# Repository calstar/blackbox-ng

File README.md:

View this project on [CADLAB.io](https://cadlab.io/project/2320). 

# blackbox-ng
This is the third major revision of STAR's black box project. Previous versions may be found on this git, and even older versions may be found on grabcad.

The major changes in this revision are the switch to kicad, the adjustment of the mounting holes pattern, and the switch to a more reliable linear regulator.

The project is seperated into a main logging board, and several spi daughter boards which can be chained together on an ffc cable and mounted about the vehicle.

## Daughter Boards

At present all daughter boards use jumpers to select the appropriate chipselect lines, but pin mappings are designed to allow us to chain an arbitrary number of devices on a single chain using 74 series shift registers. They also all share a common hole pattern and form factor.

### adxl372

This daughter board has a footprint for the adxl372, as well as a footprint for it's breakout board. The adxl372 is a relatively high bandwidth mems accelerometer that we plan on using to derive vibration data from.

### Debug Board (aka vronsky-daughter)

This board has a .1" header so that it can be used to access the signals of all the pins on its connector. It also has a footprint for a high speed barometric pressure sensor, in order to serve as a backup logging system for the pitot tube project.

### BMP388

This board is currently under development by Zitao and an attachment for STAR's next standard barometric pressure sensor. It is not yet production ready, but will likely be going out in the next board run.

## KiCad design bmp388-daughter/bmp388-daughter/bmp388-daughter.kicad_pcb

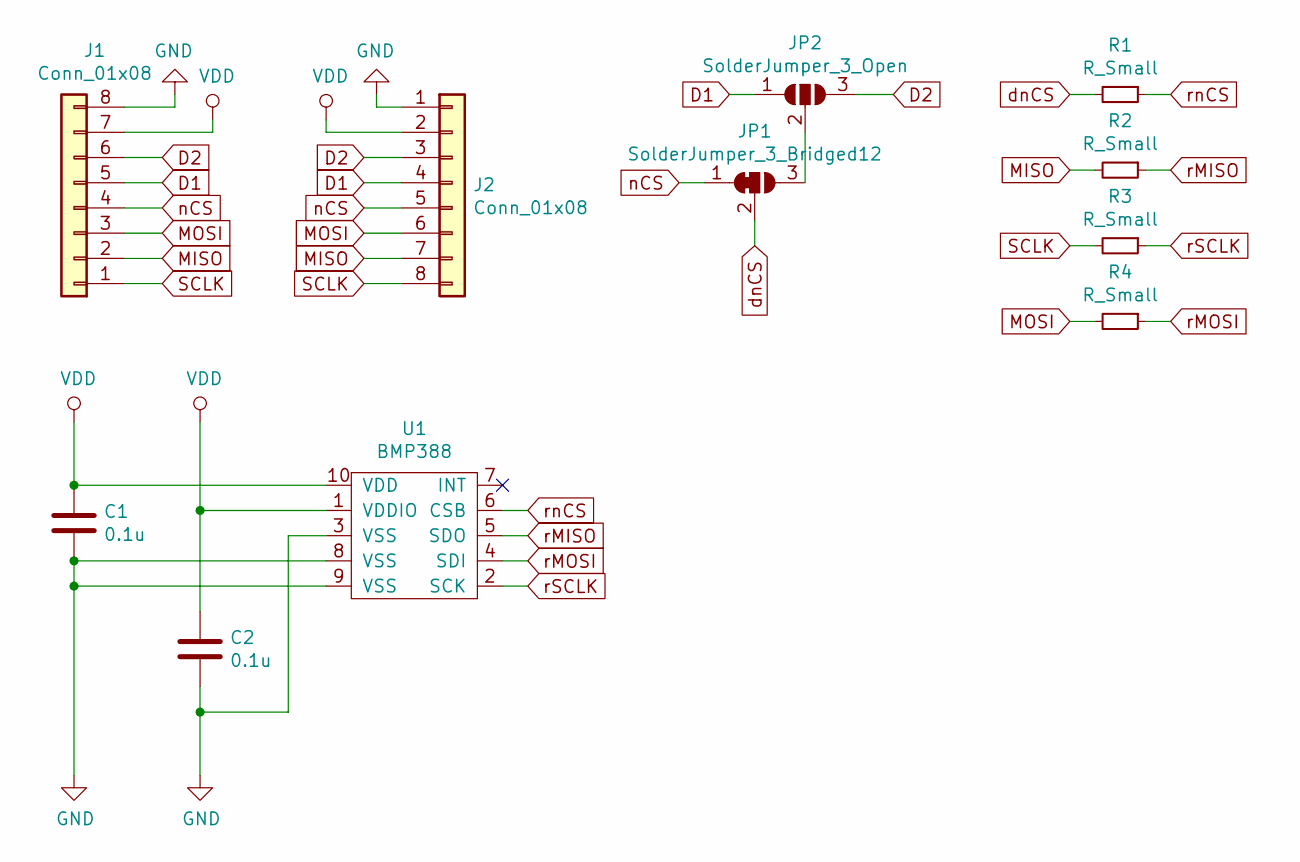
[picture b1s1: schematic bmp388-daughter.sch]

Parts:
C1, C2: 0.1u; C_0603_1608Metric_Pad1.05x0.95mm_HandSolder
J1, J2: Conn_01x08; 505110-0892
JP1: SolderJumper_3_Bridged12; SolderJumper-3_P1.3mm_Bridged2Bar12_Pad1.0x1.5mm
JP2: SolderJumper_3_Open; SolderJumper-3_P1.3mm_Open_Pad1.0x1.5mm
R1, R2, R3, R4: R_Small; R_0603_1608Metric_Pad1.05x0.95mm_HandSolder
U1: BMP388

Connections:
D1: J1.5, J2.4, JP2.1 (A)
D2: J1.6, J2.3, JP2.3 (B)
GND: C1.2, C2.2, J1.8, J2.1, U1.3 (VSS), U1.8 (VSS), U1.9 (VSS)
MISO: J1.2, J2.7, R2.2
MOSI: J1.3, J2.6, R4.2
unnamed: JP1.3 (B), JP2.2 (C)
SCLK: J1.1, J2.8, R3.2
VDD: C1.1, C2.1, J1.7, J2.2, U1.1 (VDDIO), U1.10 (VDD)
dnCS: JP1.2 (C), R1.2
nCS: J1.4, J2.5, JP1.1 (A)
rMISO: R2.1, U1.5 (SDO)
rMOSI: R4.1, U1.4 (SDI)
rSCLK: R3.1, U1.2 (SCK)
rnCS: R1.1, U1.6 (CSB)

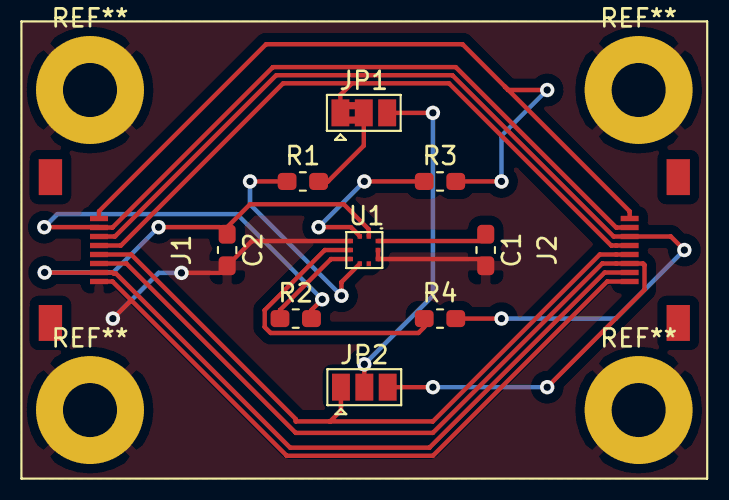
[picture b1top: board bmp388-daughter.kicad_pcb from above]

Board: 2 copper layers, 11 parts (0 on the bottom side), 14 nets.

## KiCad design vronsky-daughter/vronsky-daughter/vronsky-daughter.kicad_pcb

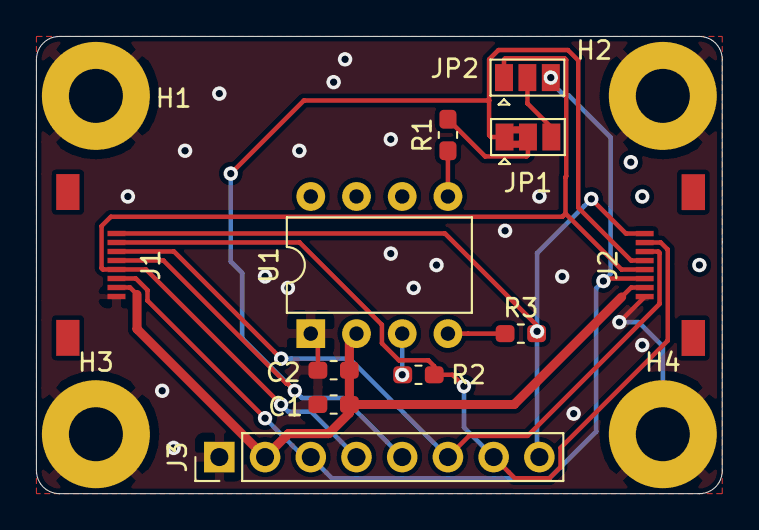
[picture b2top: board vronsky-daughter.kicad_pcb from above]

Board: 2 copper layers, 38.1 x 25.4 mm, 15 parts (0 on the bottom side), 13 nets.

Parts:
C1: 1u; C_0603_1608Metric_Pad1.05x0.95mm_HandSolder
C2: 0.1u; C_0603_1608Metric_Pad1.05x0.95mm_HandSolder
H1, H2, H3, H4: MountingHole_3mm_Pad
J1, J2: Conn_01x08; 505110-0892
J3: Conn_01x08_Male; PinHeader_1x08_P2.54mm_Vertical
JP1: SolderJumper_3_Bridged12; SolderJumper-3_P1.3mm_Bridged2Bar12_Pad1.0x1.5mm
JP2: SolderJumper_3_Open; SolderJumper-3_P1.3mm_Open_Pad1.0x1.5mm
R1, R2, R3: R_Small; R_0603_1608Metric_Pad1.05x0.95mm_HandSolder
U1: HSCSPI; DIP-8_W7.62mm

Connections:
D1: J1.5, J2.4, J3.4, JP2.1
D2: J1.6, J2.3, J3.3, JP2.3
GND: C1.1, C2.1, H1.1, H2.1, H3.1, H4.1, J1.8, J2.1, J3.1, U1.1
MISO: J1.2, J2.7, J3.7, R2.2
MOSI: J1.3, J2.6, J3.6
unnamed: JP1.3, JP2.2
SCLK: J1.1, J2.8, J3.8, R3.2
VDD: C1.2, C2.2, J1.7, J2.2, J3.2, U1.2
dnCS: JP1.2, R1.2
nCS: J1.4, J2.5, J3.5, JP1.1
rMISO: R2.1, U1.3
rSCLK: R3.1, U1.4
rnCS: R1.1, U1.5

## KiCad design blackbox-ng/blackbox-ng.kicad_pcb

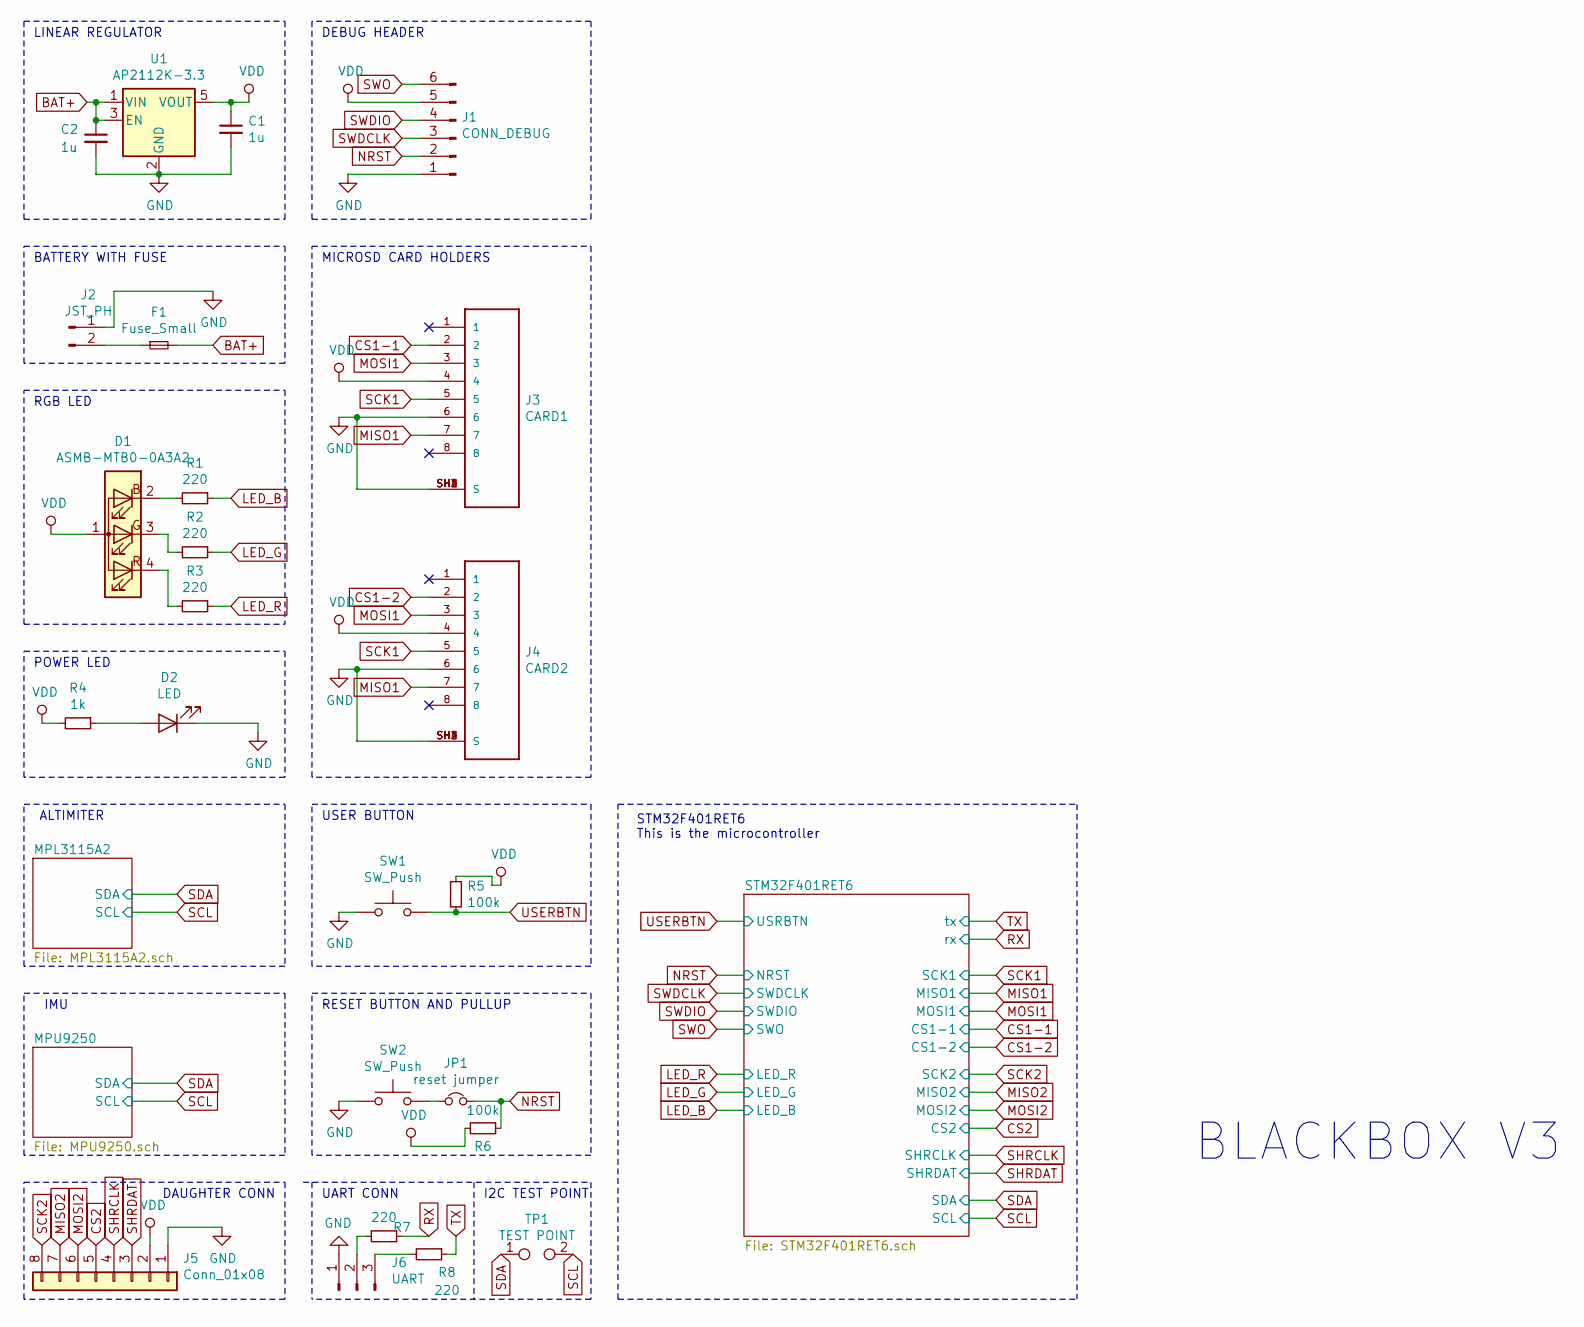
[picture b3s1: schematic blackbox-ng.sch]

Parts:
C1, C2: 1u; C_0603_1608Metric_Pad1.05x0.95mm_HandSolder
D1: ASMB-MTB0-0A3A2; LED_Avago_PLCC4_3.2x2.8mm_CW
D2: LED; LED_0603_1608Metric_Castellated
F1: Fuse_Small; Fuse_0603_1608Metric_Pad1.05x0.95mm_HandSolder
J1: CONN_DEBUG; PinHeader_1x06_P2.54mm_Vertical
J2: JST_PH; JST_PH_B2B-PH-K_1x02_P2.00mm_Vertical
J3: CARD1; MOLEX_500901-0801
J4: CARD2; MOLEX_500901-0801
J5: Conn_01x08; 505110-0892
J6: UART; PinHeader_1x03_P2.54mm_Vertical
JP1: reset jumper; SolderJumper-2_P1.3mm_Bridged2Bar_Pad1.0x1.5mm
R1, R2, R3, R7, R8: 220; R_0603_1608Metric_Pad1.05x0.95mm_HandSolder
R4: 1k; R_0603_1608Metric_Pad1.05x0.95mm_HandSolder
R5, R6: 100k; R_0603_1608Metric_Pad1.05x0.95mm_HandSolder
SW1, SW2: SW_Push; SW_SPST_B3S-1000
TP1: TEST POINT; TestPoint_2Pads_Pitch2.54mm_Drill0.8mm
U1: AP2112K-3.3; SOT-23-5

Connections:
BAT+: C2.1, F1.2, U1.1 (VIN), U1.3 (EN)
CS1-1: J3.2; also elsewhere on the board
CS1-2: J4.2; also elsewhere on the board
CS2: J5.5; also elsewhere on the board
GND: C1.2, C2.2, D2.1 (K), J1.1, J2.1, J3.6, J3.SH1 (S), J3.SH2 (S), J3.SH3 (S), J3.SH4 (S), J4.6, J4.SH1 (S), J4.SH2 (S), J4.SH3 (S), J4.SH4 (S), J5.1, J6.1, SW1.1, SW2.1, U1.2 (GND); also elsewhere on the board
LED_B: R1.1; also elsewhere on the board
LED_G: R2.1; also elsewhere on the board
LED_R: R3.1; also elsewhere on the board
MISO1: J3.7, J4.7; also elsewhere on the board
MISO2: J5.7; also elsewhere on the board
MOSI1: J3.3, J4.3; also elsewhere on the board
MOSI2: J5.6; also elsewhere on the board
NRST: J1.2, JP1.2, R6.1; also elsewhere on the board
unnamed: D1.2 (BK), R1.2
unnamed: D1.3 (GK), R2.2
unnamed: D1.4 (RK), R3.2
unnamed: D2.2 (A), R4.1
unnamed: F1.1, J2.2
unnamed: J6.2, R7.2
unnamed: J6.3, R8.2
unnamed: JP1.1, SW2.2
RX: R7.1; also elsewhere on the board
SCK1: J3.5, J4.5; also elsewhere on the board
SCK2: J5.8; also elsewhere on the board
SCL: TP1.2; also elsewhere on the board
SDA: TP1.1; also elsewhere on the board
SHRCLK: J5.4; also elsewhere on the board
SHRDAT: J5.3; also elsewhere on the board
SWDCLK: J1.3; also elsewhere on the board
SWDIO: J1.4; also elsewhere on the board
SWO: J1.6; also elsewhere on the board
TX: R8.1; also elsewhere on the board
USERBTN: R5.2, SW1.2; also elsewhere on the board
VDD: C1.1, D1.1 (A), J1.5, J3.4, J4.4, J5.2, R4.2, R5.1, R6.2, U1.5 (VOUT); also elsewhere on the board

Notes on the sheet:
LINEAR REGULATOR
BATTERY WITH FUSE
RGB LED
POWER LED
ALTIMITER
IMU
DEBUG HEADER
MICROSD CARD HOLDERS
USER BUTTON
RESET BUTTON AND PULLUP
DAUGHTER CONN
UART CONN
I2C TEST POINT
STM32F401RET6 This is the microcontroller
BLACKBOX V3

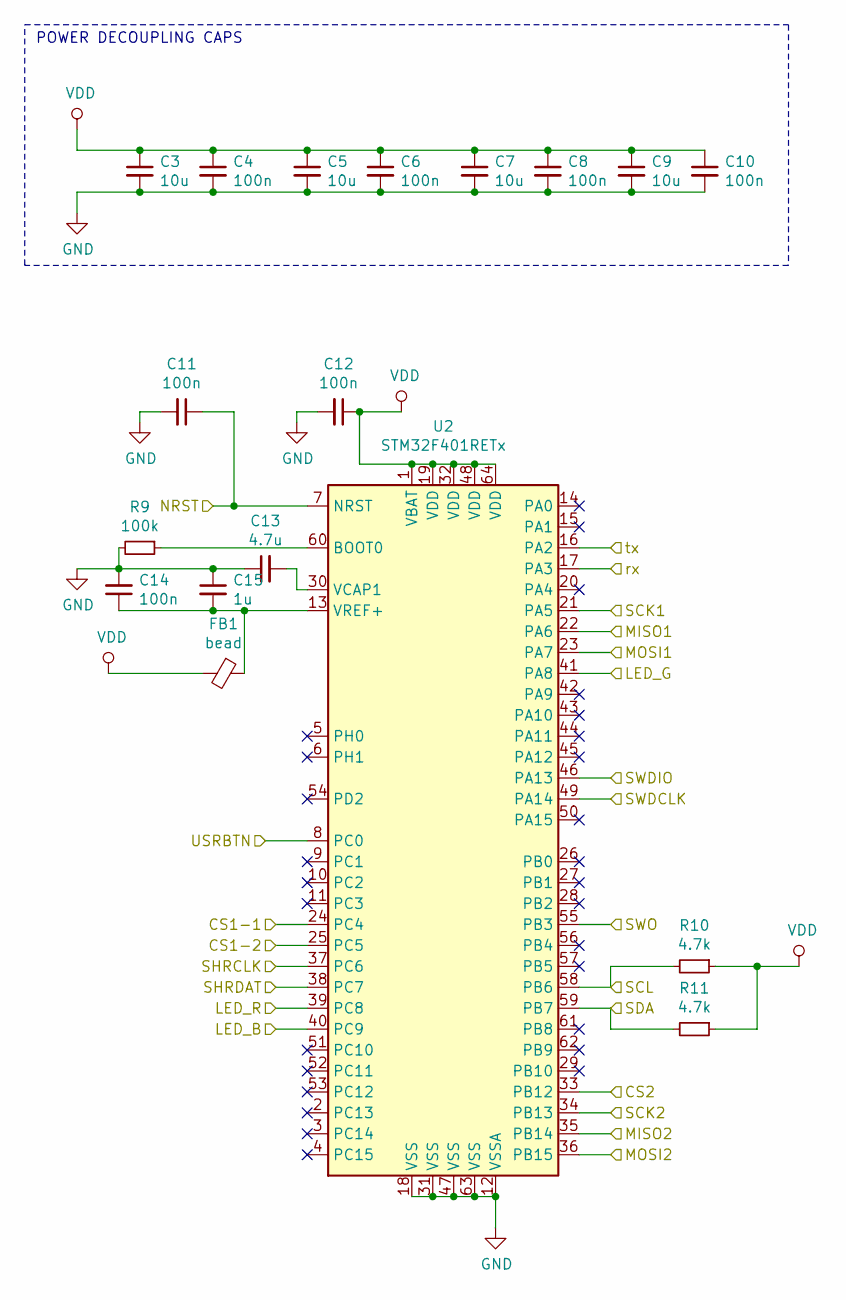
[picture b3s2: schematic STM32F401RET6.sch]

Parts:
C3, C5, C7, C9: 10u; C_0603_1608Metric_Pad1.05x0.95mm_HandSolder
C4, C6, C8, C10, C11, C12, C14: 100n; C_0603_1608Metric_Pad1.05x0.95mm_HandSolder
C13: 4.7u; C_0603_1608Metric_Pad1.05x0.95mm_HandSolder
C15: 1u; C_0603_1608Metric_Pad1.05x0.95mm_HandSolder
FB1: bead; L_0603_1608Metric_Pad1.05x0.95mm_HandSolder
R9: 100k; R_0603_1608Metric_Pad1.05x0.95mm_HandSolder
R10, R11: 4.7k; R_0603_1608Metric_Pad1.05x0.95mm_HandSolder
U2: STM32F401RETx; LQFP-64_10x10mm_P0.5mm

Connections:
CS1-1: U2.24 (PC4); also elsewhere on the board
CS1-2: U2.25 (PC5); also elsewhere on the board
CS2: U2.33 (PB12); also elsewhere on the board
GND: C3.2, C4.2, C5.2, C6.2, C7.2, C8.2, C9.2, C10.2, C11.2, C12.2, C13.1, C14.2, C15.1, R9.2, U2.12 (VSSA), U2.18 (VSS), U2.31 (VSS), U2.47 (VSS), U2.63 (VSS); also elsewhere on the board
LED_B: U2.40 (PC9); also elsewhere on the board
LED_G: U2.41 (PA8); also elsewhere on the board
LED_R: U2.39 (PC8); also elsewhere on the board
MISO1: U2.22 (PA6); also elsewhere on the board
MISO2: U2.35 (PB14); also elsewhere on the board
MOSI1: U2.23 (PA7); also elsewhere on the board
MOSI2: U2.36 (PB15); also elsewhere on the board
NRST: C11.1, U2.7 (NRST); also elsewhere on the board
unnamed: C13.2, U2.30 (VCAP1)
unnamed: C14.1, C15.2, FB1.1, U2.13 (VREF+)
unnamed: R9.1, U2.60 (BOOT0)
RX: U2.17 (PA3); also elsewhere on the board
SCK1: U2.21 (PA5); also elsewhere on the board
SCK2: U2.34 (PB13); also elsewhere on the board
SCL: R10.2, U2.58 (PB6); also elsewhere on the board
SDA: R11.2, U2.59 (PB7); also elsewhere on the board
SHRCLK: U2.37 (PC6); also elsewhere on the board
SHRDAT: U2.38 (PC7); also elsewhere on the board
SWDCLK: U2.49 (PA14); also elsewhere on the board
SWDIO: U2.46 (PA13); also elsewhere on the board
SWO: U2.55 (PB3); also elsewhere on the board
TX: U2.16 (PA2); also elsewhere on the board
USERBTN: U2.8 (PC0); also elsewhere on the board
VDD: C3.1, C4.1, C5.1, C6.1, C7.1, C8.1, C9.1, C10.1, C12.1, FB1.2, R10.1, R11.1, U2.1 (VBAT), U2.19 (VDD), U2.32 (VDD), U2.48 (VDD), U2.64 (VDD); also elsewhere on the board

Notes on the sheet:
POWER DECOUPLING CAPS

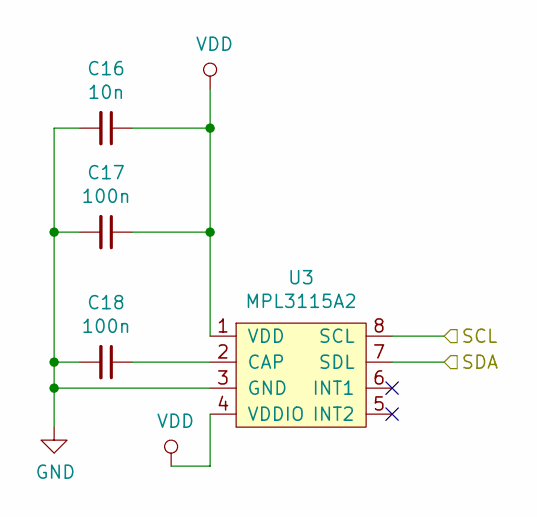
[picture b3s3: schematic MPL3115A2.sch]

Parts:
C16: 10n; C_0603_1608Metric_Pad1.05x0.95mm_HandSolder
C17, C18: 100n; C_0603_1608Metric_Pad1.05x0.95mm_HandSolder
U3: MPL3115A2; NXP_LGA-8_3x5mm_P1.25mm_H1.1mm

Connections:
GND: C16.2, C17.2, C18.2, U3.3 (GND); also elsewhere on the board
unnamed: C18.1, U3.2 (CAP)
SCL: U3.8 (SCL); also elsewhere on the board
SDA: U3.7 (SDL); also elsewhere on the board
VDD: C16.1, C17.1, U3.1 (VDD), U3.4 (VDDIO); also elsewhere on the board

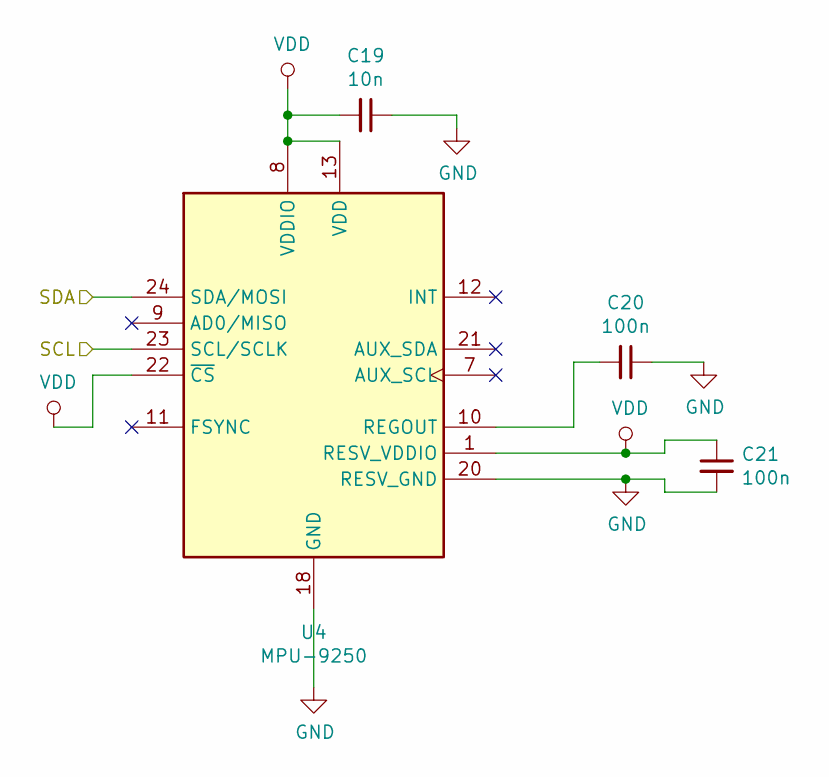
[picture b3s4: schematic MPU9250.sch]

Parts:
C19: 10n; C_0603_1608Metric_Pad1.05x0.95mm_HandSolder
C20, C21: 100n; C_0603_1608Metric_Pad1.05x0.95mm_HandSolder
U4: MPU-9250; InvenSense_QFN-24_3x3mm_P0.4mm

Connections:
GND: C19.1, C20.1, C21.2, U4.18 (GND), U4.20 (RESV_GND); also elsewhere on the board
unnamed: C20.2, U4.10 (REGOUT)
SCL: U4.23 (SCL/SCLK); also elsewhere on the board
SDA: U4.24 (SDA/MOSI); also elsewhere on the board
VDD: C19.2, C21.1, U4.1 (RESV_VDDIO), U4.8 (VDDIO), U4.13 (VDD), U4.22 (~CS); also elsewhere on the board

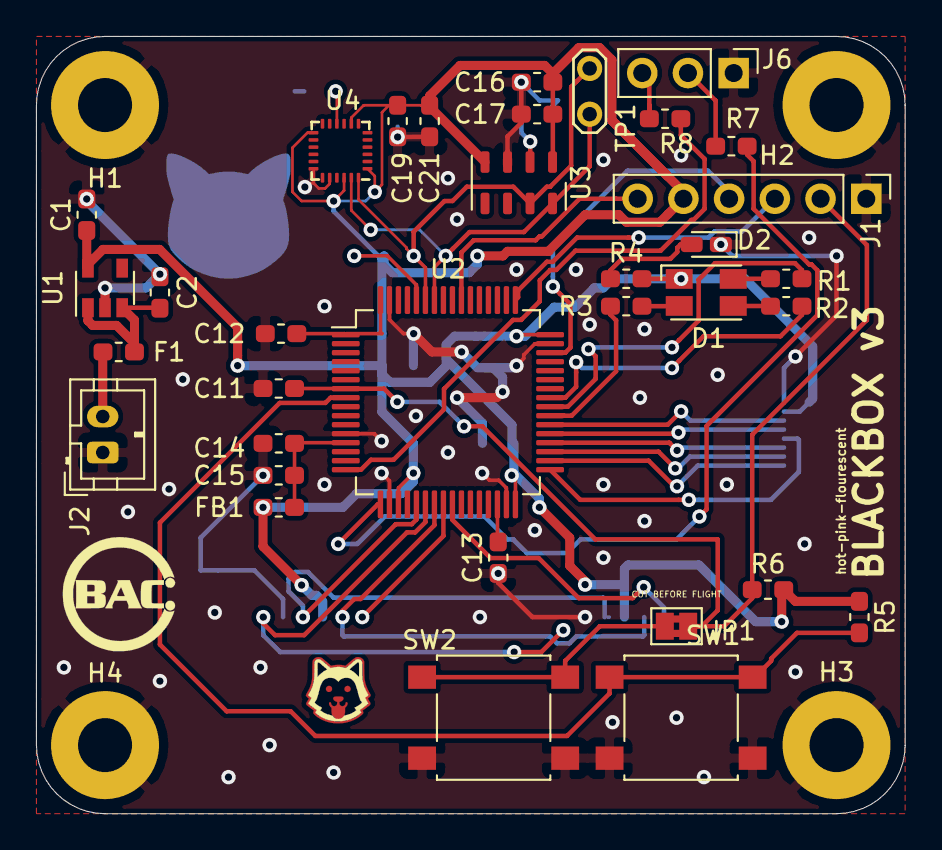
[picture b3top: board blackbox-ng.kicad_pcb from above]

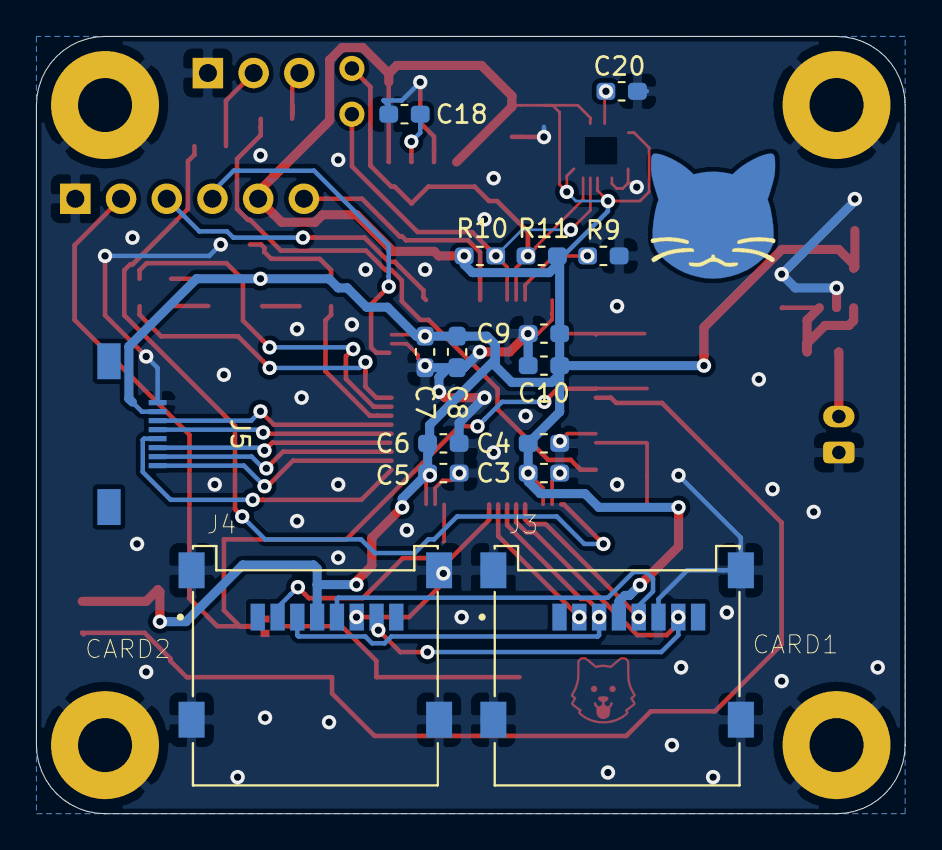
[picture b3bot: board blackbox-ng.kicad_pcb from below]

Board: 2 copper layers, 48.3 x 43.2 mm, 54 parts (16 on the bottom side), 39 nets.

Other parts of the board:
H1, H2, H3, H4: MountingHole_3mm_Pad

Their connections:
GND: H1.1, H2.1, H3.1, H4.1; also elsewhere on the board

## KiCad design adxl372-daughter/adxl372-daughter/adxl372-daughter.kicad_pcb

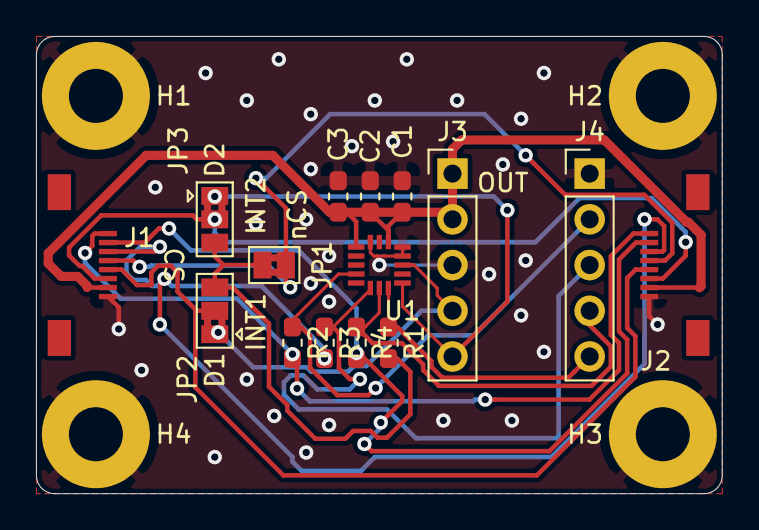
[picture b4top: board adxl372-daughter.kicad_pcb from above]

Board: 2 copper layers, 38.1 x 25.4 mm, 19 parts (0 on the bottom side), 15 nets.

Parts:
C1: 1u; C_0603_1608Metric_Pad1.05x0.95mm_HandSolder
C2, C3: 0.1u; C_0603_1608Metric_Pad1.05x0.95mm_HandSolder
H1, H2, H3, H4: MountingHole_3mm_Pad
J1, J2: Conn_01x08; 505110-0892
J3, J4: Conn_01x05_Female; PinHeader_1x05_P2.54mm_Vertical
JP1: SolderJumper_2_Bridged; SolderJumper-2_P1.3mm_Bridged2Bar_Pad1.0x1.5mm
JP2, JP3: SolderJumper_3_Bridged12; SolderJumper-3_P1.3mm_Bridged2Bar12_Pad1.0x1.5mm
R1, R2, R3, R4: 0; R_0603_1608Metric_Pad1.05x0.95mm_HandSolder
U1: ADXL372

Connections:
D1: J1.5, J2.4, JP2.2
D2: J1.6, J2.3, JP3.2
GND: C1.1, C2.1, C3.1, H1.1, H2.1, H3.1, H4.1, J1.8, J2.1, J3.3, J4.1, U1.12, U1.13, U1.16
INT1: J3.4, JP2.1, U1.11
INT2: J3.5, JP3.1, U1.9
MISO: J1.2, J2.7, R4.2
MOSI: J1.3, J2.6, R3.2
SCLK: J1.1, J2.8, R2.2
VDD: C1.2, C2.2, C3.2, J1.7, J2.2, J3.1, J3.2, U1.1, U1.14
dnCS: JP1.2, JP2.3, JP3.3, R1.2
nCS: J1.4, J2.5, JP1.1
rMISO: J4.4, R4.1, U1.7
rMOSI: J4.3, R3.1, U1.6
rSCLK: J4.2, R2.1, U1.4
rnCS: J4.5, R1.1, U1.8

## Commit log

2019-11-27 start project and create stm sheet
2019-11-27 Backlink to CADLAB.io has been added.
2019-11-27 add linear regulator
2019-11-27 cach :/
2019-11-27 Remove cadlab cruft
2019-11-27 add battery
2019-11-27 add power led
2019-11-27 add mpl
2019-11-27 add MPU9250 IMU
2019-11-27 add sdcard and buttons
2019-11-28 complete schematic
2019-11-28 assign footprints
2019-11-28 do initial layout
2019-11-28 add logos
2019-11-28 updated logo
2019-11-28 floof
2019-11-28 add very important board functionality
2019-11-29 something something golden bears
2020-02-18 cleanup layout
2020-02-18 add daughter part 2
2020-02-18 fleshed out daughter card
2020-02-18 made suggested edits
2020-02-18 improved ground conectivity
2020-02-18 make pass drc
2020-02-19 add breakout
2020-03-08 BMP388 Breakout done
